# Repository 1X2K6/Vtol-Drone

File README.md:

# Vtol-Drone

# No-Control-Surface Vtol Drone

A custom VTOL search-and-rescue (SAR) drone built **without control surfaces** Pitch, roll, and yaw are achieved strictly through **differential motor thrust and motorized motor/pod movement**.

For SAR operations, the drone uses a **4mm front thermal camera**, **dual RunCam FPV cameras**, a **3-way video switcher** over a **1.2 GHz** link, and under the drone near the front is a **24 GHz mmWave human-detection radar** sweeping **180° on a servo**—with radar visuals displayed on a **2.4" TFT screen** and relayed live to the ground station by the second FPV camera.

---

## Table of Contents
* Features
* Hardware & Bill of Materials
* System Architecture
* Sensor & Camera Layout
* Build & Setup Notes
* Repository Structure
* Safety Notice

---

## Features
* **Control-Surface-Free Flight:** Eliminates linkages and hinged aerodynamic surfaces; relies purely on thrust allocation and motor/pod articulation.
* **180° Sweeping Human-Detection Radar:** A **24 GHz mmWave radar** mounted on a **180° servo** beneath the fuselage scans wide sectors for human presence/micro-motion.
* **Optical Radar Relay:** An **ESP32** renders radar detections onto a **2.4" TFT screen**, which is captured by **RunCam FPV #2** and transmitted to the ground via the **3-way video switcher**—requiring zero extra telemetry downlink hardware.
* **Tri-Feed 1.2 GHz Video Link:** Switch mid-flight between frontal thermal search, top-nose navigation FPV, and the live TFT radar display.

---

## 🛠 Hardware & Bill of Materials

### Flight, Propulsion & Control
* **Flight Controller:** Matek H743 (Qty: 1) — Main autopilot & motor/actuator mixing
* **Motors:** EMAX ECO II 3115 900KV (Qty: 4) — Hover & forward-flight propulsion
* **ESCs:** Hobbywing Skywalker V2 80A (Qty: 4) — Brushless motor speed control
* **Battery:** 10,000 mAh (Qty: 1) — High-capacity flight pack
* **RC Receiver:** RadioMaster XR3 Nano (Qty: 1) — Control & telemetry link
* **RC Transmitter:** RadioMaster TX16S MkIII (Qty: 1) — Ground pilot controller
* **Radar Sweep Servo:** 180° Servo (Qty: 1) — Sweeps the 24 GHz mmWave radar under the drone

### Sensors, Display & Video
* **Thermal Camera:** 4mm Lens Thermal Camera (Qty: 1) — Front-mounted heat-signature search
* **FPV Camera #1:** RunCam FPV Camera (Qty: 1) — Top-nose forward flight view
* **FPV Camera #2:** RunCam FPV Camera (Qty: 1) — Aimed at 2.4" TFT screen to relay radar data
* **Video Switcher:** 3-Way Video Switcher (Qty: 1) — Selects between Thermal, FPV #1, and FPV #2
* **Video Link:** 1.2 GHz VTX & VRX (Qty: 1 set) — Long-range analog video transmission
* **mmWave Radar:** 24 GHz Human Detection Module (Qty: 1) — Sweeps 180° underneath for human detection
* **Microcontroller:** ESP32 (Qty: 1) — Reads radar UART/IO & drives TFT UI
* **Display:** 2.4" TFT Screen (Qty: 1) — Displays radar sweep & human-detection alerts

### Airframe Materials
* **Carbon Fiber Tubes:** Primary structural booms and spars
* **PolyLite LW-PLA:** Lightweight aerodynamic body and wing shells
* **Creality PETG-CF:** High-rigidity motor mounts, tilting pods, and servo brackets
* **Generic TPU:** the wing tips (also can be used for camera mounts and the radar pod)

## 📡 Sensor & Camera Layout
* **Front Nose: 4mm thermal camera with an unobstructed forward/downward search view.
* **Top of Nose: RunCam FPV #1 for standard pilot situational awareness and landing.
* **Underbelly: 24 GHz mmWave radar mounted on a 180° sweep servo for wide-arc human detection.
* **Internal Bay: ESP32 + 2.4" TFT screen enclosed with RunCam FPV #2 in a light-shielded shroud to prevent screen glare on the video feed.

## Build & Setup Notes
* **Bench Verification (Props Off): Confirm motor spin directions, motor/pod movement endpoints, and failsafe behavior before attaching propellers.
* **TFT Shroud: Enclose the 2.4" TFT screen and RunCam FPV #2 in a dark matte printed shroud (PETG-CF or TPU) so ambient sunlight does not wash out the radar display.
* **RF Separation: Keep the 1.2 GHz VTX antenna separated from the RadioMaster XR3 Nano and 24 GHz radar to minimize RF interference.

## ⚠️ NOTE: The 3d model files are not mine it is bought i just modified some of the models and uploaded them to build the drone you would need to buy the stl files.

## Below,is a picture of the drone.

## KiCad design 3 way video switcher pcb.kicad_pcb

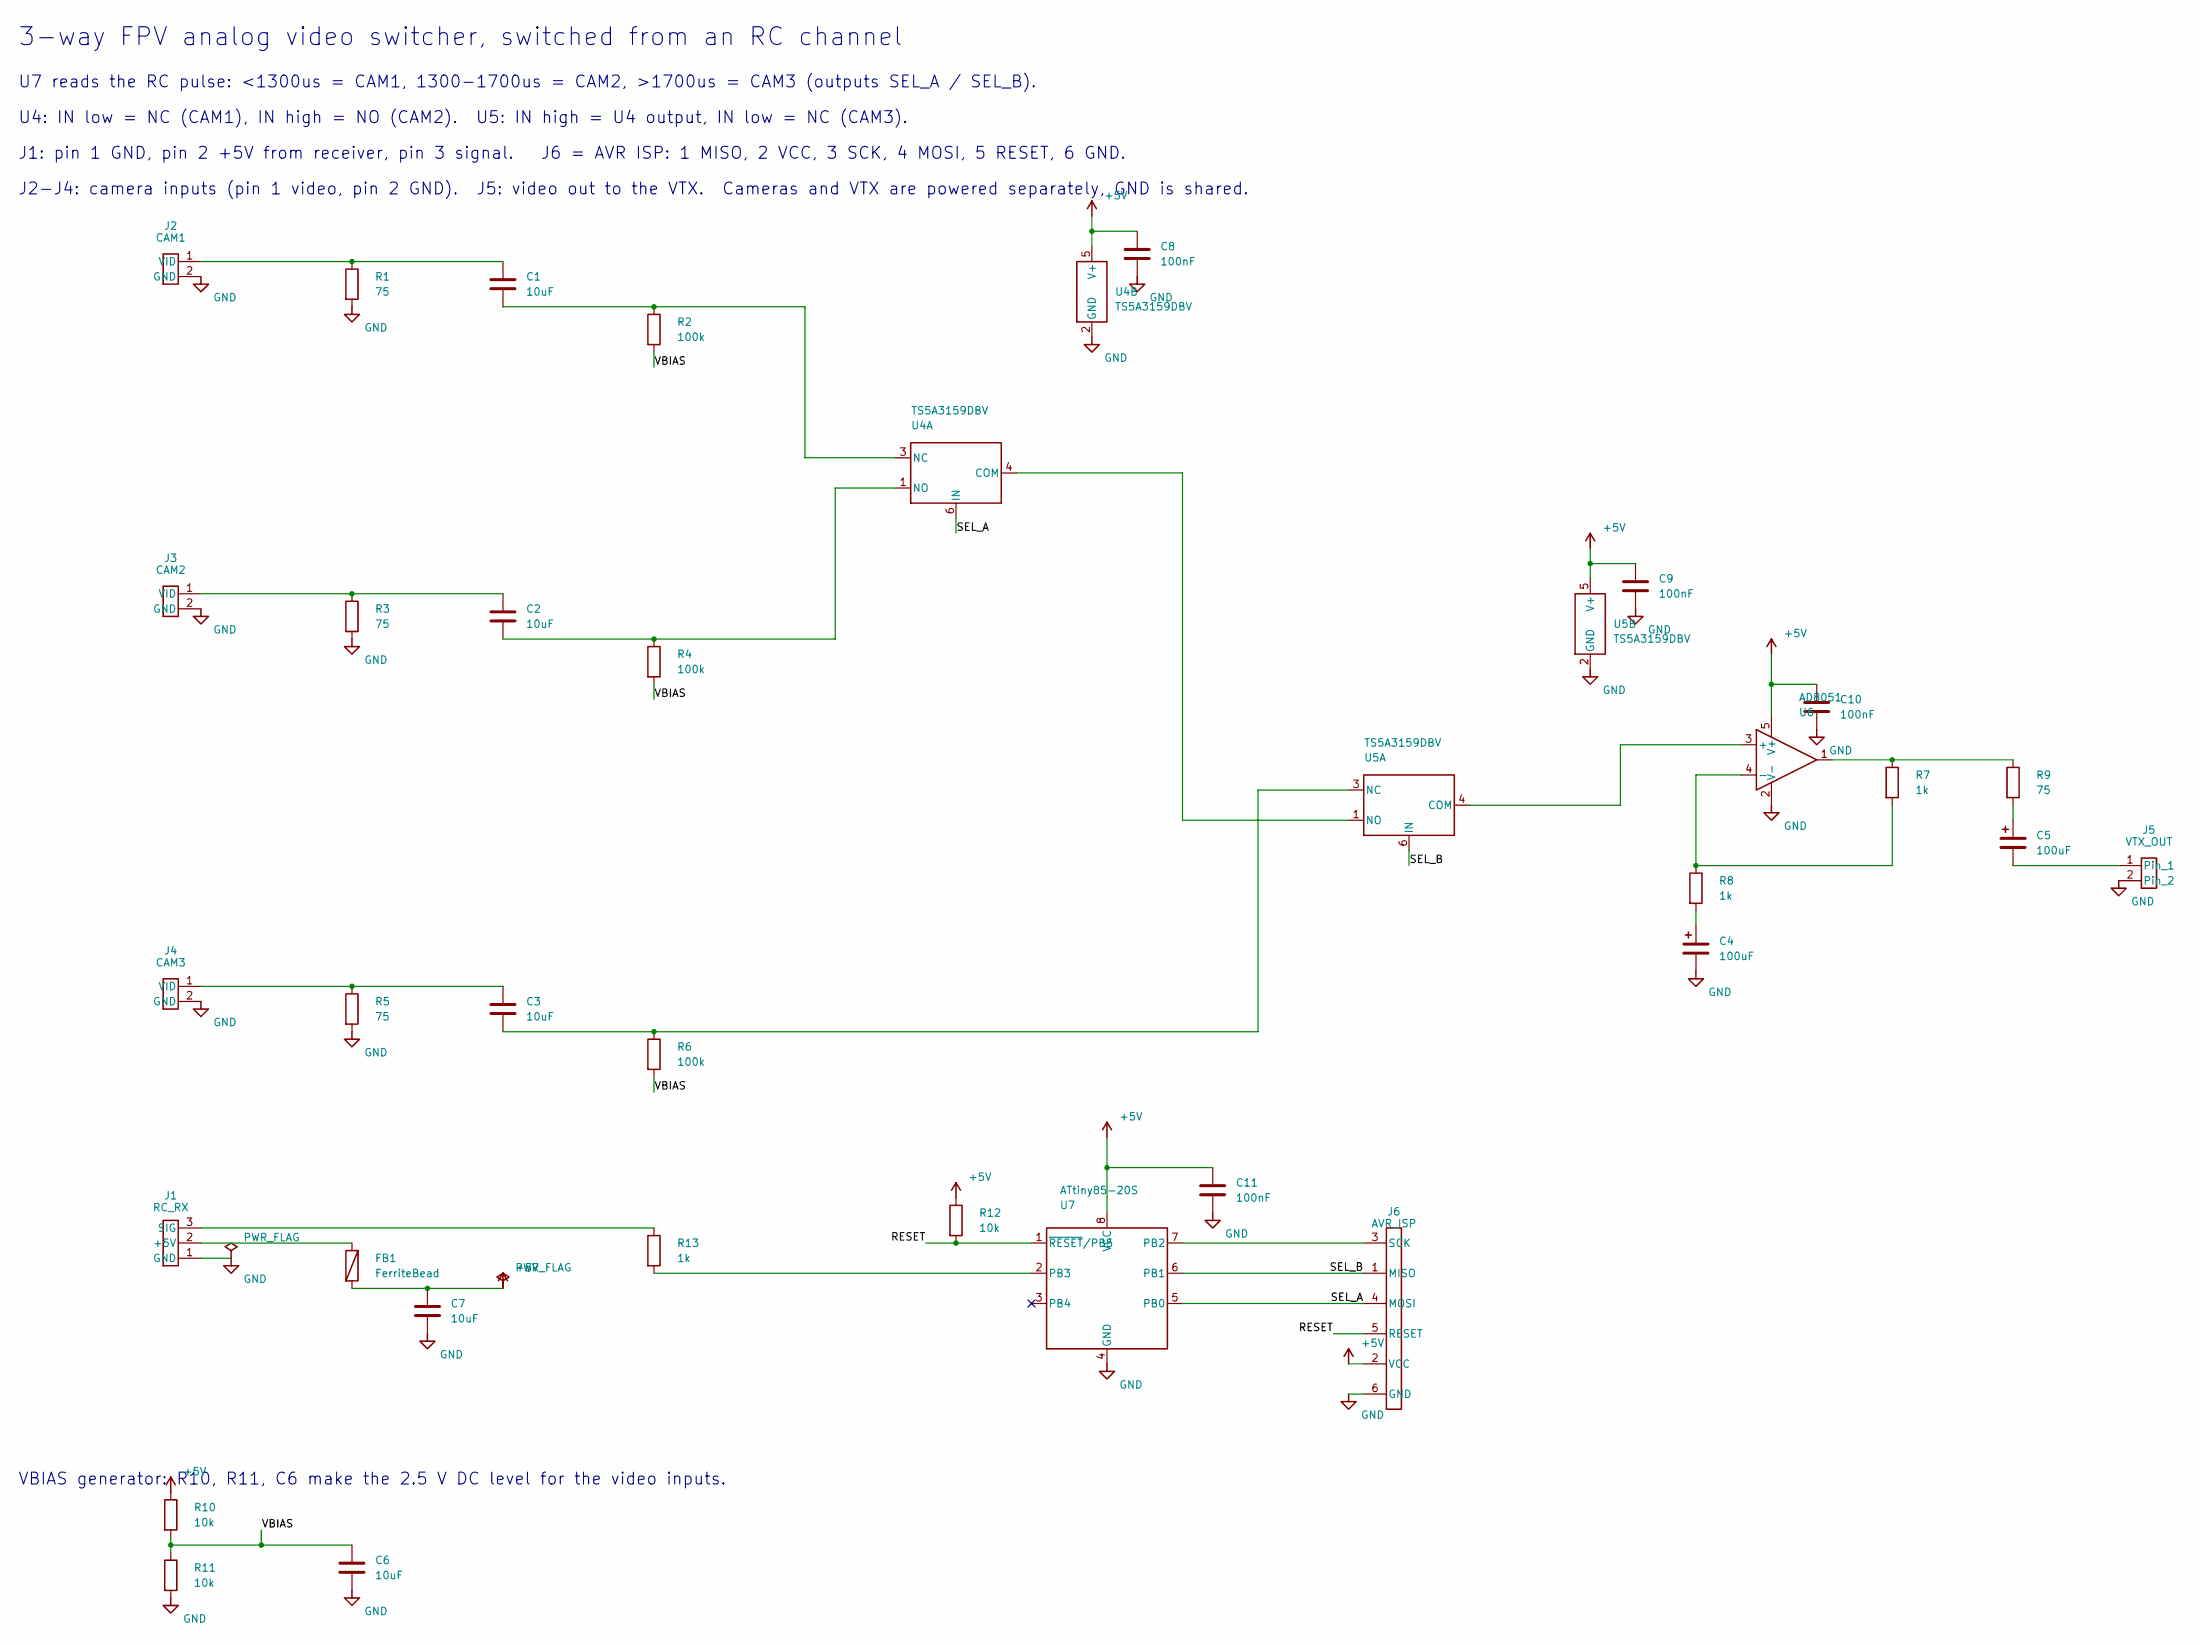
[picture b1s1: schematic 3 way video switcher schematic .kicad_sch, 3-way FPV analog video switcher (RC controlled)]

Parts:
C1, C2, C3, C6, C7: 10uF; C_0805_2012Metric
C4, C5: 100uF; CP_Elec_6.3x5.4
C8, C9, C10, C11: 100nF; C_0603_1608Metric
FB1: FerriteBead; L_0805_2012Metric
J1: RC_RX; PinHeader_1x03_P2.54mm_Vertical
J2: CAM1; PinHeader_1x02_P2.54mm_Vertical
J3: CAM2; PinHeader_1x02_P2.54mm_Vertical
J4: CAM3; PinHeader_1x02_P2.54mm_Vertical
J5: VTX_OUT; PinHeader_1x02_P2.54mm_Vertical
J6: AVR_ISP; PinHeader_2x03_P2.54mm_Vertical
R1, R3, R5, R9: 75; R_0603_1608Metric
R2, R4, R6: 100k; R_0603_1608Metric
R7, R8, R13: 1k; R_0603_1608Metric
R10, R11, R12: 10k; R_0603_1608Metric
U4, U5: TS5A3159DBV; SOT-23-6
U6: AD8051; SOT-23-5
U7: ATtiny85-20S; SOIC-8_5.3x5.3mm_P1.27mm

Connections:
+5V: C7.1, C8.1, C9.1, C10.1, C11.1, FB1.2, J6.2 (VCC), R10.1, R12.1, U4.5 (V+), U5.5 (V+), U6.5 (V+), U7.8 (VCC)
/RESET: J6.5 (RESET), R12.2, U7.1 (~RESET/PB5)
/SEL_A: J6.4 (MOSI), U4.6 (IN), U7.5 (PB0)
/SEL_B: J6.1 (MISO), U5.6 (IN), U7.6 (PB1)
/VBIAS: C6.1, R2.2, R4.2, R6.2, R10.2, R11.1
GND: C4.2, C6.2, C7.2, C8.2, C9.2, C10.2, C11.2, J1.1 (GND), J2.2 (GND), J3.2 (GND), J4.2 (GND), J5.2, J6.6 (GND), R1.2, R3.2, R5.2, R11.2, U4.2 (GND), U5.2 (GND), U6.2 (V-), U7.4 (GND)
unnamed: C1.1, J2.1 (VID), R1.1
unnamed: C1.2, R2.1, U4.3 (NC)
unnamed: C2.1, J3.1 (VID), R3.1
unnamed: C2.2, R4.1, U4.1 (NO)
unnamed: C3.1, J4.1 (VID), R5.1
unnamed: C3.2, R6.1, U5.3 (NC)
unnamed: C4.1, R8.2
unnamed: C5.1, R9.2
unnamed: C5.2, J5.1
unnamed: FB1.1, J1.2 (+5V)
unnamed: J1.3 (SIG), R13.1
unnamed: J6.3 (SCK), U7.7 (PB2)
unnamed: R7.1, R9.1, U6.1
unnamed: R7.2, R8.1, U6.4 (-)
unnamed: R13.2, U7.2 (PB3)
unnamed: U4.4 (COM), U5.1 (NO)
unnamed: U5.4 (COM), U6.3 (+)

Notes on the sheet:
3-way FPV analog video switcher, switched from an RC channel
U7 reads the RC pulse: <1300us = CAM1, 1300-1700us = CAM2, >1700us = CAM3 (outputs SEL_A / SEL_B).
U4: IN low = NC (CAM1), IN high = NO (CAM2). U5: IN high = U4 output, IN low = NC (CAM3).
J1: pin 1 GND, pin 2 +5V from receiver, pin 3 signal. J6 = AVR ISP: 1 MISO, 2 VCC, 3 SCK, 4 MOSI, 5 RESET, 6 GND.
J2-J4: camera inputs (pin 1 video, pin 2 GND). J5: video out to the VTX. Cameras and VTX are powered separately, GND is shared.
VBIAS generator: R10, R11, C6 make the 2.5 V DC level for the video inputs.

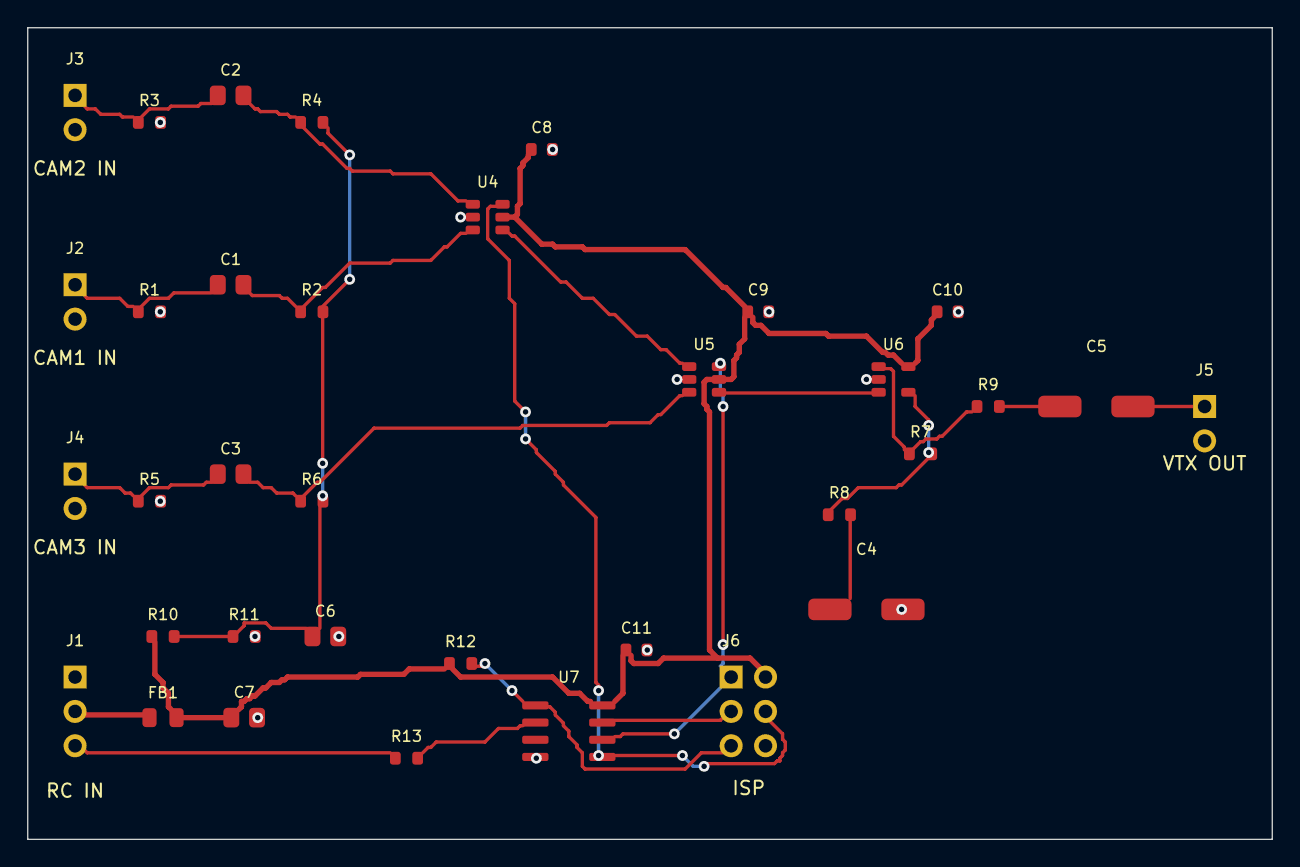
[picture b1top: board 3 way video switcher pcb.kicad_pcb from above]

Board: 2 copper layers, 92.0 x 60.0 mm, 35 parts (0 on the bottom side), 23 nets.
